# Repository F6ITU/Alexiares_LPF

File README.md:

# Alexiares_LPF
This repository contains the up to date version of the OpenHPSDR Low Pass Filter project(Alexiares frontend). 

**Important notice** : please check the "Branch" pull-down menu to see the different versions of the pcb

This work is protected by the TAPR Open Hardware Licence https://www.tapr.org/ohl.html

Original work by Graham Haddock, KE9H and Phil Harman, VK6APH.

3D image of the board are stored in the "images" folder (3D and pcb planes)

This folder also include "real life" pictures of the board, Vector Analyzer capture of the filter's characteristics and a pdf file of the schematic

Board's dimensions 10x15cm , 4 layers

So far, the Alex project under Kicad contains: 

AlexI2C

Alexandrie 

Alexiares_Coax_Out

Alexiares_HPF

Alexiares_LPF (this one)

Mentor

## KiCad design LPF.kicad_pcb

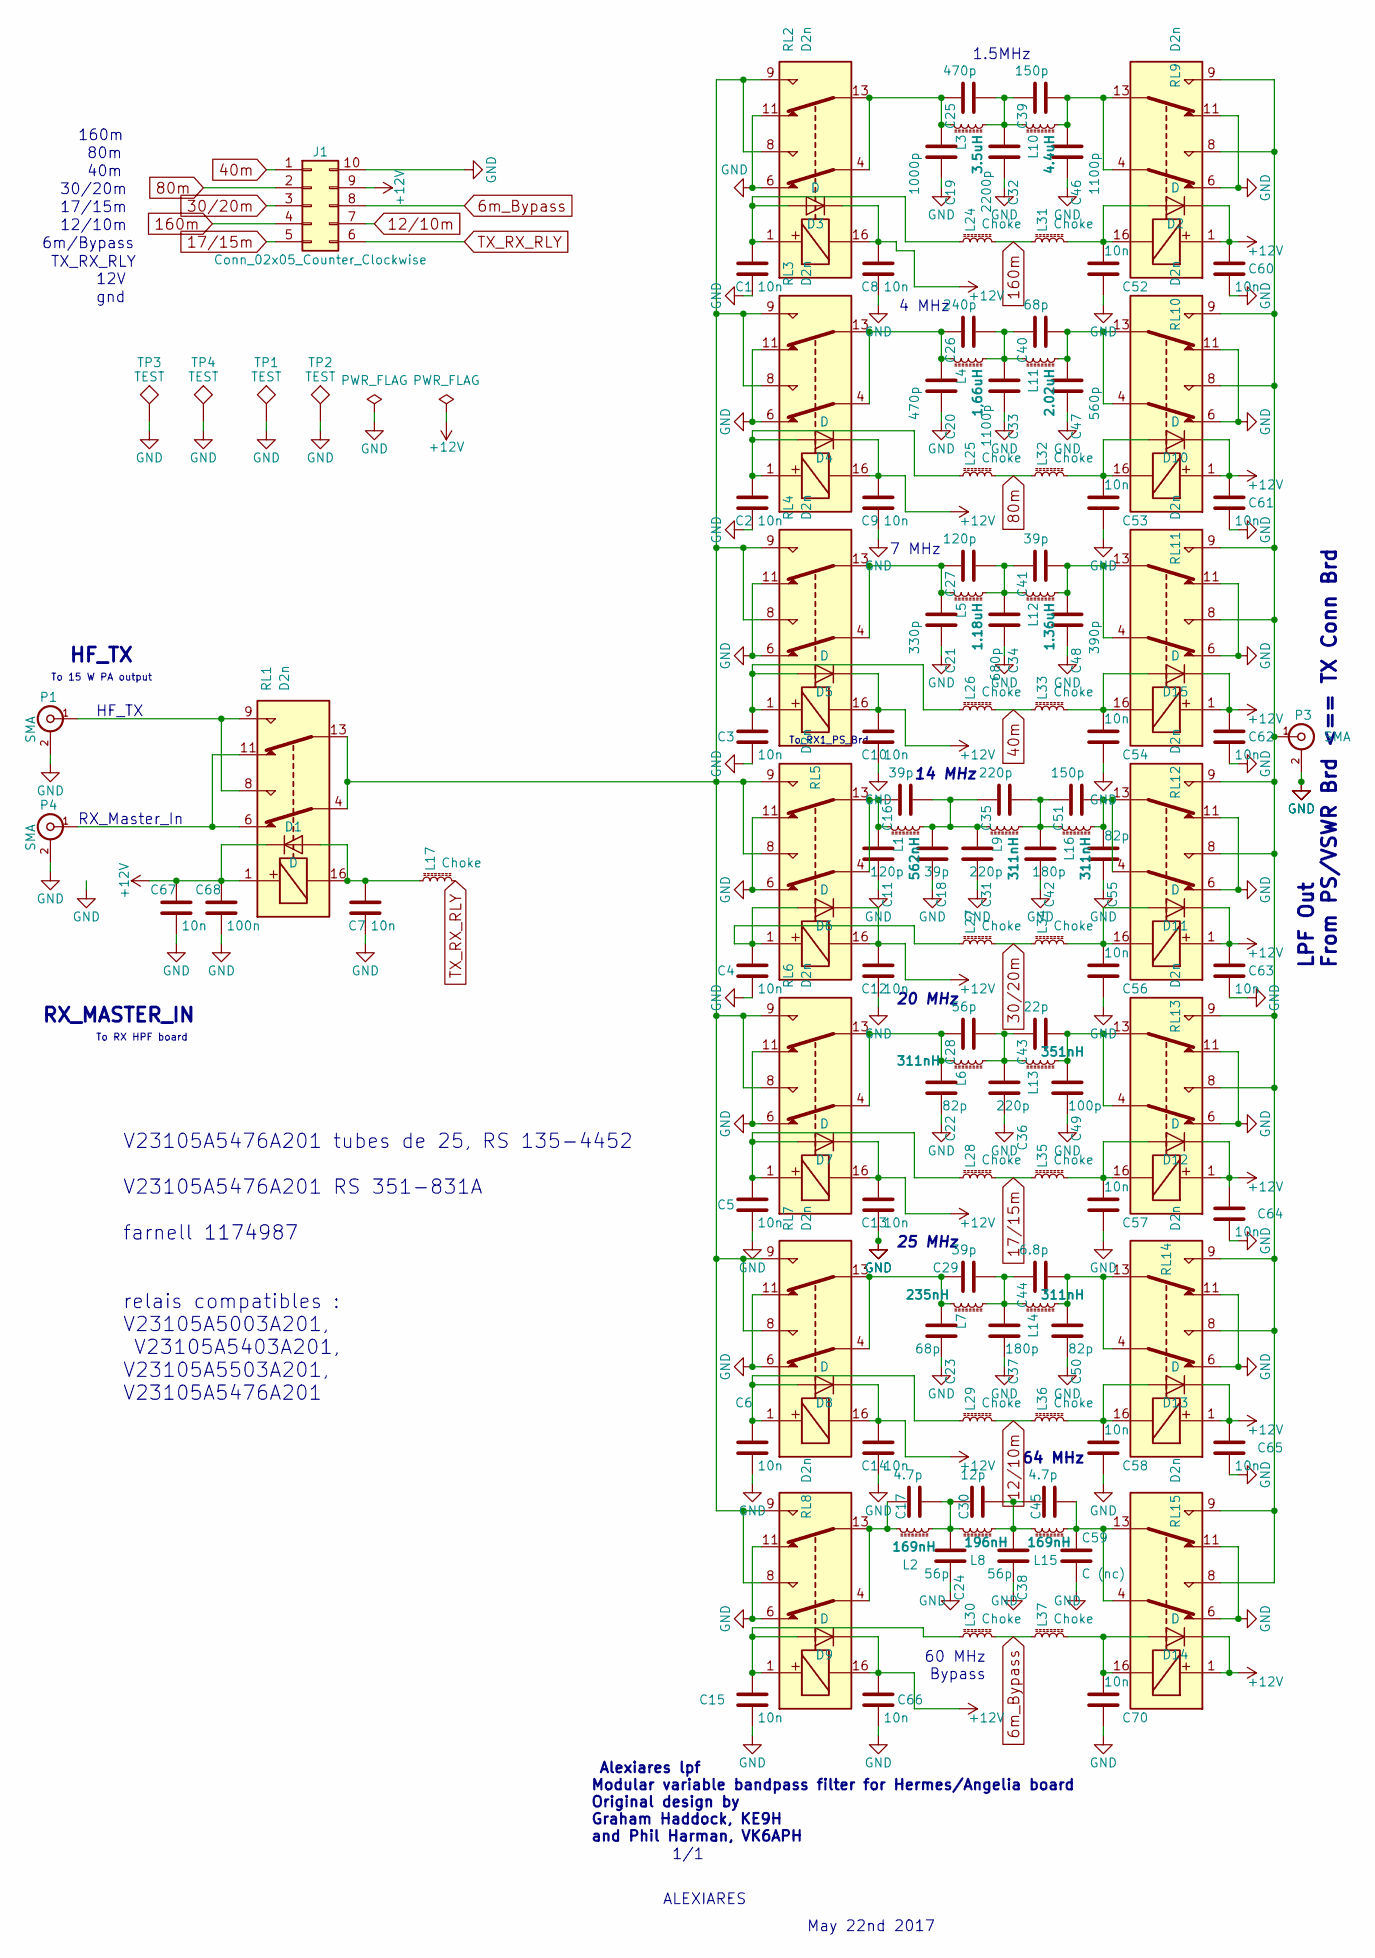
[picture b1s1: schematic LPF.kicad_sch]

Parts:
C1, C2, C3, C4, C5, C6, C7, C8, C9, C10, C12, C13, C14, C15, C52, C53, C54, C56, C57, C58, C60, C61, C62, C63, C64, C65, C66, C67, C70: 10n; C_0805_2012Metric_Pad1.15x1.40mm_HandSolder
C11, C27: 120p; ATC_500_HandSoldering
C16, C18, C29, C41: 39p; ATC_500_HandSoldering
C17, C45: 4.7p; ATC_500_HandSoldering
C19: 1000p; ATC_500_HandSoldering
C20, C25: 470p; ATC_500_HandSoldering
C21: 330p; ATC_500_HandSoldering
C22, C50, C55: 82p; ATC_500_HandSoldering
C23, C40: 68p; ATC_500_HandSoldering
C24, C28, C38: 56p; ATC_500_HandSoldering
C26: 240p; ATC_500_HandSoldering
C30: 12p; ATC_500_HandSoldering
C31, C35, C36: 220p; ATC_500_HandSoldering
C32: 2200p; ATC_500_HandSoldering
C33, C46: 1100p; ATC_500_HandSoldering
C34: 680p; ATC_500_HandSoldering
C37, C42: 180p; ATC_500_HandSoldering
C39, C51: 150p; ATC_500_HandSoldering
C43: 22p; ATC_500_HandSoldering
C44: 6.8p; ATC_500_HandSoldering
C47: 560p; ATC_500_HandSoldering
C48: 390p; ATC_500_HandSoldering
C49: 100p; ATC_500_HandSoldering
C59: C (nc); ATC_500_HandSoldering
C68: 100n; C_0805_2012Metric_Pad1.15x1.40mm_HandSolder
D1, D2, D3, D4, D5, D6, D7, D8, D9, D10, D11, D12, D13, D14, D15: D; D_SMB
J1: Conn_02x05_Counter_Clockwise; PinHeader_2x05_P2.54mm_Vertical
L1: 562nH; T50_V_THT
L2, L15: 169nH; T50_V_THT
L3: 3.5uH; T50_V_THT
L4: 1,66uH; T50_V_THT
L5: 1.18uH; T50_V_THT
L6, L9, L14, L16: 311nH; T50_V_THT
L7: 235nH; T50_V_THT
L8: 196nH; T50_V_THT
L10: 4.4uH; T50_V_THT
L11: 2.02uH; T50_V_THT
L12: 1.36uH; T50_V_THT
L13: 351nH; T50_V_THT
L17, L24, L25, L26, L27, L28, L29, L30, L31, L32, L33, L34, L35, L36, L37: Choke; L_0805_2012Metric_Pad1.15x1.40mm_HandSolder
P1, P3, P4: SMA; SMA_PINS
RL1, RL2, RL3, RL4, RL5, RL6, RL7, RL8, RL9, RL10, RL11, RL12, RL13, RL14, RL15: D2n
TP1, TP2, TP3, TP4: TEST; MountingHole_3.5mm_Pad

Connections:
6m_Bypass: J1.8, L30.2, L37.1
12/10m: J1.7, L29.2, L36.1
17/15m: J1.5, L28.2, L35.1
30/20m: J1.3, L27.2, L34.1
40m: J1.1, L26.2, L33.1
80m: J1.2, L25.2, L32.1
160m: J1.4, L24.2, L31.1
+12V: C8.1, C9.1, C10.1, C12.1, C13.1, C14.1, C60.1, C61.1, C62.1, C63.1, C64.1, C65.1, C66.1, C67.1, C68.1, D1.1 (K), D2.1 (K), D3.1 (K), D4.1 (K), D5.1 (K), D6.1 (K), D7.1 (K), D8.1 (K), D9.1 (K), D10.1 (K), D11.1 (K), D12.1 (K), D13.1 (K), D14.1 (K), D15.1 (K), J1.9, RL1.1, RL2.16, RL3.16, RL4.16, RL5.16, RL6.16, RL7.16, RL8.16, RL9.1, RL10.1, RL11.1, RL12.1, RL13.1, RL14.1, RL15.1
GND: C1.2, C2.2, C3.2, C4.2, C5.2, C6.2, C7.2, C8.2, C9.2, C10.2, C11.1, C12.2, C13.2, C14.2, C15.2, C18.1, C19.1, C20.1, C21.1, C22.1, C23.1, C24.1, C31.1, C32.1, C33.1, C34.1, C36.1, C37.1, C38.1, C42.1, C46.1, C47.1, C48.1, C49.1, C50.1, C52.1, C53.1, C54.1, C55.1, C56.1, C57.1, C58.1, C59.2, C60.2, C61.2, C62.2, C63.2, C64.2, C65.2, C66.2, C67.2, C68.2, C70.1, J1.10, P1.2 (Ext), P3.2 (Ext), P4.2 (Ext), RL2.6, RL2.11, RL3.6, RL3.11, RL4.6, RL4.11, RL5.6, RL5.11, RL6.6, RL6.11, RL7.6, RL7.11, RL8.6, RL8.11, RL9.6, RL9.11, RL10.6, RL10.11, RL11.6, RL11.11, RL12.6, RL12.11, RL13.6, RL13.11, RL14.6, RL14.11, RL15.6, RL15.11, TP1.1, TP2.1, TP3.1, TP4.1
unnamed: C1.1, D3.2 (A), L24.1, RL2.1
unnamed: C2.1, D4.2 (A), L25.1, RL3.1
unnamed: C3.1, D5.2 (A), L26.1, RL4.1
unnamed: C4.1, D6.2 (A), L27.1, RL5.1
unnamed: C5.1, D7.2 (A), L28.1, RL6.1
unnamed: C6.1, D8.2 (A), L29.1, RL7.1
unnamed: C7.1, D1.2 (A), L17.1, RL1.16
unnamed: C11.2, C16.1, L1.1, RL5.4, RL5.13
unnamed: C15.1, D9.2 (A), L30.1, RL8.1
unnamed: C16.2, C18.2, C31.2, C35.1, L1.2, L9.1
unnamed: C17.1, L2.1, RL8.4, RL8.13
unnamed: C17.2, C24.2, C30.1, L2.2, L8.1
unnamed: C19.2, C25.1, L3.1, RL2.4, RL2.13
unnamed: C20.2, C26.1, L4.1, RL3.4, RL3.13
unnamed: C21.2, C27.1, L5.1, RL4.4, RL4.13
unnamed: C22.2, C28.1, L6.1, RL6.4, RL6.13
unnamed: C23.2, C29.1, L7.1, RL7.4, RL7.13
unnamed: C25.2, C32.2, C39.1, L3.2, L10.1
unnamed: C26.2, C33.2, C40.1, L4.2, L11.1
unnamed: C27.2, C34.2, C41.1, L5.2, L12.1
unnamed: C28.2, C36.2, C43.1, L6.2, L13.1
unnamed: C29.2, C37.2, C44.1, L7.2, L14.1
unnamed: C30.2, C38.2, C45.1, L8.2, L15.1
unnamed: C35.2, C42.2, C51.1, L9.2, L16.1
unnamed: C39.2, C46.2, L10.2, RL9.4, RL9.13
unnamed: C40.2, C47.2, L11.2, RL10.4, RL10.13
unnamed: C41.2, C48.2, L12.2, RL11.4, RL11.13
unnamed: C43.2, C49.2, L13.2, RL13.4, RL13.13
unnamed: C44.2, C50.2, L14.2, RL14.4, RL14.13
unnamed: C45.2, C59.1, L15.2, RL15.4, RL15.13
unnamed: C51.2, C55.2, L16.2, RL12.4, RL12.13
unnamed: C52.2, D2.2 (A), L31.2, RL9.16
unnamed: C53.2, D10.2 (A), L32.2, RL10.16
unnamed: C54.2, D15.2 (A), L33.2, RL11.16
unnamed: C56.2, D11.2 (A), L34.2, RL12.16
unnamed: C57.2, D12.2 (A), L35.2, RL13.16
unnamed: C58.2, D13.2 (A), L36.2, RL14.16
unnamed: C70.2, D14.2 (A), L37.2, RL15.16
unnamed: P1.1 (In), RL1.8, RL1.9
unnamed: P3.1 (In), RL9.8, RL9.9, RL10.8, RL10.9, RL11.8, RL11.9, RL12.8, RL12.9, RL13.8, RL13.9, RL14.8, RL14.9, RL15.8, RL15.9
unnamed: P4.1 (In), RL1.6, RL1.11
unnamed: RL1.4, RL1.13, RL2.8, RL2.9, RL3.8, RL3.9, RL4.8, RL4.9, RL5.8, RL5.9, RL6.8, RL6.9, RL7.8, RL7.9, RL8.8, RL8.9
TX_RX_RLY: J1.6, L17.2

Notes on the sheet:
gnd
25 MHz
30/20m
TX_RX_RLY
12V
ALEXIARES
160m
6m/Bypass
1/1
14 MHz
4 MHz
80m
V23105A5476A201 tubes de 25, RS 135-4452 V23105A5476A201 RS 351-831A farnell 1174987 relais compatibles : V23105A5003A201, V23105A5403A201, V23105A5503A201, V23105A5476A201
To_RX1_PS_Brd
17/15m
To 15 W PA output
1.5MHz
RX_Master_In
RX_MASTER_IN
64 MHz
LPF Out From PS/VSWR Brd <== TX Conn Brd
Alexiares lpf Modular variable bandpass filter for Hermes/Angelia board Original design by Graham Haddock, KE9H and Phil Harman, VK6APH
May 22nd 2017
HF_TX
7 MHz
20 MHz
40m
60 MHz Bypass
12/10m
To RX HPF board

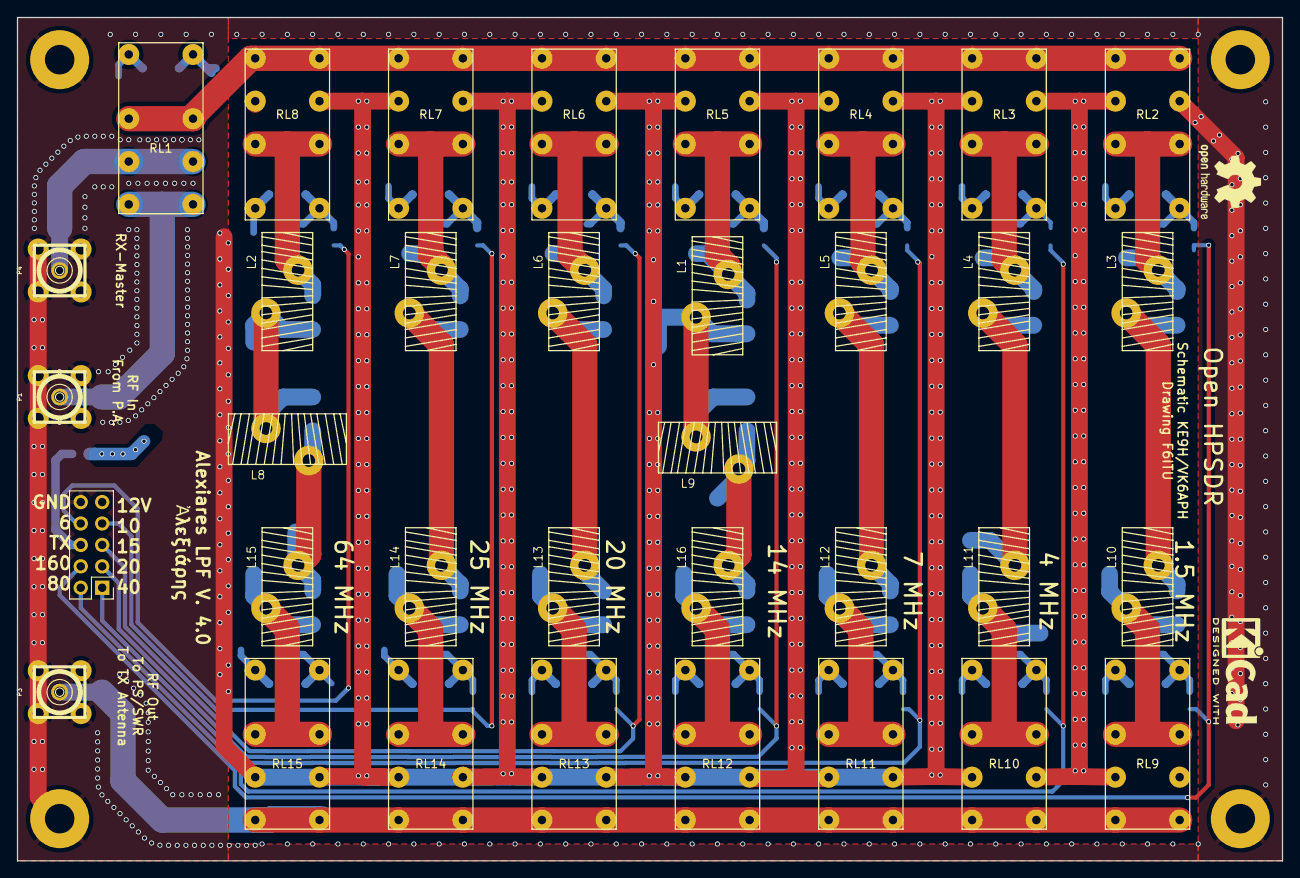
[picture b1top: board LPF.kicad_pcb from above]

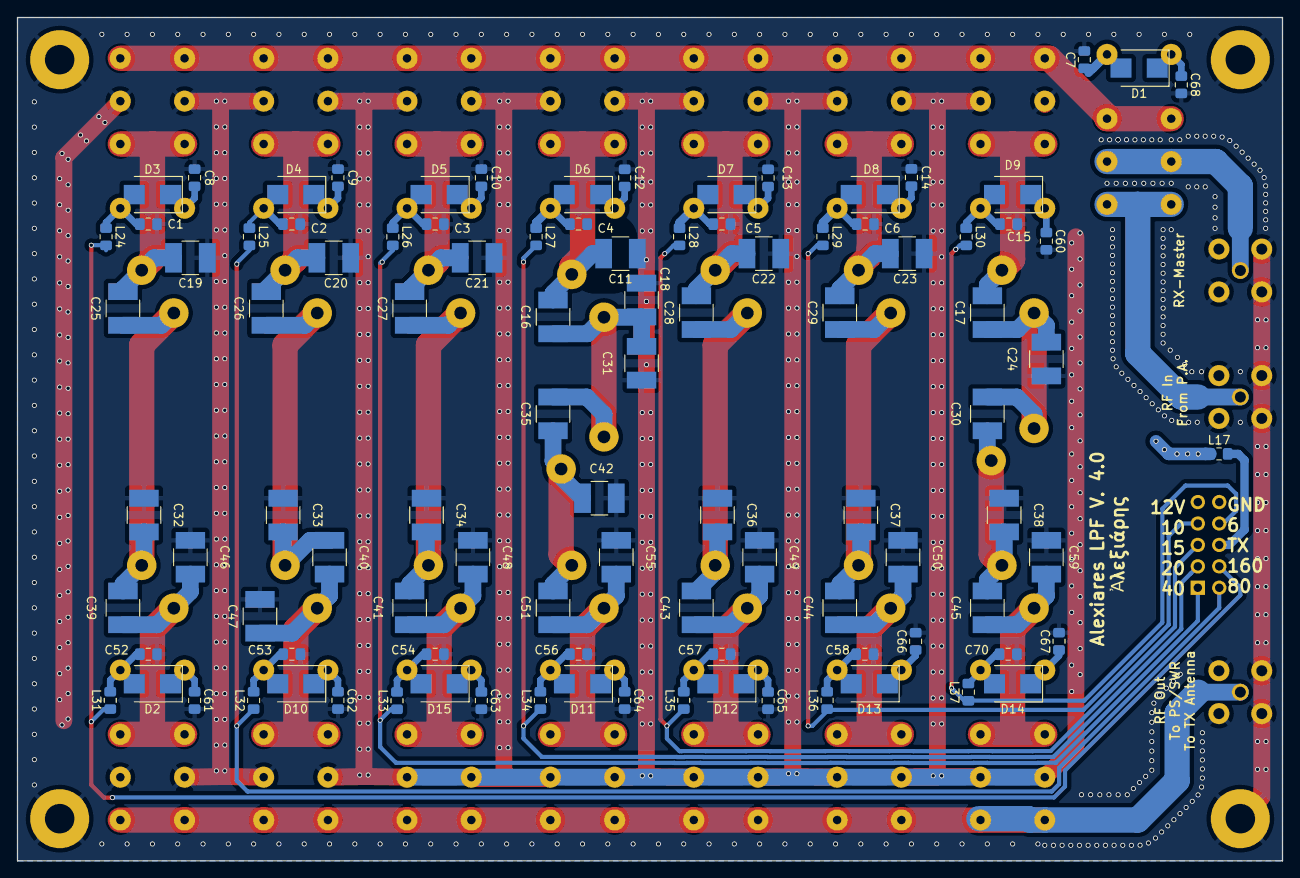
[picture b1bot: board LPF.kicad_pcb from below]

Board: 4 copper layers, 150.0 x 100.0 mm, 138 parts (99 on the bottom side), 52 nets.

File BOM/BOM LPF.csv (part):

Source:,C:\Users\marco\Documents\KiCad\Projets\Alexiares_LPF\LPF.sch,,,,,,
Date:,22/07/2020 10:55,,,,,,
Tool:,Eeschema (5.1.5)-3,,,,,,
Component Count:,134,,,,,,
Ref,Value,Footprint,Manufacturer,Type,Vendor,Reference,
C1,10n,Capacitor_SMD:C_0805_2012Metric_Pad1.15x1.40mm_HandSolder,Wurth Elektronik,MLCC,Mouser,710-885012207092,
C2,10n,Capacitor_SMD:C_0805_2012Metric_Pad1.15x1.40mm_HandSolder,Wurth Elektronik,MLCC,Mouser,710-885012207092,
C3,10n,Capacitor_SMD:C_0805_2012Metric_Pad1.15x1.40mm_HandSolder,Wurth Elektronik,MLCC,Mouser,710-885012207092,
C4,10n,Capacitor_SMD:C_0805_2012Metric_Pad1.15x1.40mm_HandSolder,Wurth Elektronik,MLCC,Mouser,710-885012207092,
C5,10n,Capacitor_SMD:C_0805_2012Metric_Pad1.15x1.40mm_HandSolder,Wurth Elektronik,MLCC,Mouser,710-885012207092,
C6,10n,Capacitor_SMD:C_0805_2012Metric_Pad1.15x1.40mm_HandSolder,Wurth Elektronik,MLCC,Mouser,710-885012207092,
C7,10n,Capacitor_SMD:C_0805_2012Metric_Pad1.15x1.40mm_HandSolder,Wurth Elektronik,MLCC,Mouser,710-885012207092,
C8,10n,Capacitor_SMD:C_0805_2012Metric_Pad1.15x1.40mm_HandSolder,Wurth Elektronik,MLCC,Mouser,710-885012207092,
C9,10n,Capacitor_SMD:C_0805_2012Metric_Pad1.15x1.40mm_HandSolder,Wurth Elektronik,MLCC,Mouser,710-885012207092,
C10,10n,Capacitor_SMD:C_0805_2012Metric_Pad1.15x1.40mm_HandSolder,Wurth Elektronik,MLCC,Mouser,710-885012207092,
C11,120p,Vishay HiFreq 1111 MLCC,Vishay Vitramon,MLCC 500V,Mouser,VJ1111D121KXGAT,
C12,10n,Capacitor_SMD:C_0805_2012Metric_Pad1.15x1.40mm_HandSolder,Wurth Elektronik,MLCC,Mouser,710-885012207092,
C13,10n,Capacitor_SMD:C_0805_2012Metric_Pad1.15x1.40mm_HandSolder,Wurth Elektronik,MLCC,Mouser,710-885012207092,
C14,10n,Capacitor_SMD:C_0805_2012Metric_Pad1.15x1.40mm_HandSolder,Wurth Elektronik,MLCC,Mouser,710-885012207092,
C15,10n,Capacitor_SMD:C_0805_2012Metric_Pad1.15x1.40mm_HandSolder,Wurth Elektronik,MLCC,Mouser,710-885012207092,
C16,39p,Vishay HiFreq 1111 MLCC,Vishay Vitramon,MLCC 500V,Mouser,VJ1111D390JXLAJ,
C17,4.7p,Vishay HiFreq 1111 MLCC,Vishay Vitramon,MLCC 500V,Mouser,VJ1111D4R7BXLQJ,
C18,39p,Vishay HiFreq 1111 MLCC,Vishay Vitramon,MLCC 500V,Mouser,VJ1111D390JXLAJ,
C19,1000p,Johanson,johanson 1812,MLCC 500V,Mouser,501S43N102JV4E,
C20,470p,Vishay HiFreq 1111 MLCC,Vishay Vitramon,MLCC 500V,Mouser,VJ1111D471KXLAJ,
C21,330p,Vishay HiFreq 1111 MLCC,Vishay Vitramon,MLCC 500V,Mouser,VJ1111D331JXLAJ,
C22,82p,Vishay HiFreq 1111 MLCC,Vishay Vitramon,MLCC 500V,Mouser,VJ1111D820GXGQJ,
C23,68p,Vishay HiFreq 1111 MLCC,Vishay Vitramon,MLCC 500V,Mouser,VJ1111D680GXLQJ,
C24,56p,Vishay HiFreq 1111 MLCC,Vishay Vitramon,MLCC 500V,Mouser,VJ1111D560GXLQJ,
C25,470p,Vishay HiFreq 1111 MLCC,Vishay Vitramon,MLCC 500V,Mouser,VJ1111D471KXLAJ,
C26,240p,Vishay HiFreq 1111 MLCC,Vishay Vitramon,MLCC 500V,Mouser,VJ1111D241JXLAJ,
C27,120p,Vishay HiFreq 1111 MLCC,Vishay Vitramon,MLCC 500V,Mouser,VJ1111D121KXGAT,
C28,56p,Vishay HiFreq 1111 MLCC,Vishay Vitramon,MLCC 500V,Mouser,VJ1111D560GXLQJ,
C29,39p,Vishay HiFreq 1111 MLCC,Vishay Vitramon,MLCC 500V,Mouser,VJ1111D390JXLAJ,
C30,12p,Vishay HiFreq 1111 MLCC,Vishay Vitramon,MLCC 500V,Mouser,VJ1111D120GLGQJ,
C31,220p,Vishay HiFreq 1111 MLCC,Vishay Vitramon,MLCC 500V,Mouser,VJ1111D221JXLAJ,
C32,2200p,Johanson,Johanson 1812,MLCC 1000V,Mouser,102S43N222KV4E,
C33,1100p,Vishay HiFreq 1111 MLCC,Vishay Vitramon,MLCC 500V,Mouser,VJ1111D102KXDAT,VJ1111D101JXLAJ
C34,680p,Johanson,johanson 1210,MLCC 1000V,Mouser,102S41N681KV4E,
C35,220p,Vishay HiFreq 1111 MLCC,Vishay Vitramon,MLCC 500V,Mouser,VJ1111D221JXLAJ,
C36,220p,Vishay HiFreq 1111 MLCC,Vishay Vitramon,MLCC 500V,Mouser,VJ1111D221JXLAJ,
C37,180p,Vishay HiFreq 1111 MLCC,Vishay Vitramon,MLCC 500V,Mouser,VJ1111D181JXLAJ,
C38,56p,Vishay HiFreq 1111 MLCC,Vishay Vitramon,MLCC 500V,Mouser,VJ1111D560GXLQJ,
C39,150p,Vishay HiFreq 1111 MLCC,Vishay Vitramon,MLCC 500V,Mouser,VJ1111D151GXLQJ,
C40,68p,Vishay HiFreq 1111 MLCC,Vishay Vitramon,MLCC 500V,Mouser,VJ1111D680GXLQJ,
C41,39p,Vishay HiFreq 1111 MLCC,Vishay Vitramon,MLCC 500V,Mouser,VJ1111D390JXLAJ,
C42,180p,Vishay HiFreq 1111 MLCC,Vishay Vitramon,MLCC 500V,Mouser,VJ1111D181JXLAJ,
C43,22p,Vishay HiFreq 1111 MLCC,Vishay Vitramon,MLCC 500V,Mouser,VJ1111D220GLLQJ,
C44,6.8p,Vishay HiFreq 1111 MLCC,Vishay Vitramon,MLCC 500V,Mouser,VJ1111D6R8BXGQJ,
C45,4.7p,Vishay HiFreq 1111 MLCC,Vishay Vitramon,MLCC 500V,Mouser,VJ1111D4R7BXLQ,
C46,1100p,Vishay HiFreq 1111 MLCC,Vishay Vitramon,MLCC 500V,Mouser,VJ1111D102KXDAT,VJ1111D101JXLAJ
C47,560p,Johanson,Johanson 1210,MLCC 500V,Mouser,501S41N561KV4E,
C48,390p,Vishay HiFreq 1111 MLCC,Vishay Vitramon,MLCC 500V,Mouser,VJ1111D391KXLAJ,
C49,100p,Vishay HiFreq 1111 MLCC,Vishay Vitramon,MLCC 500V,Mouser,VJ1111D101JXLAJ,
C50,82p,Vishay HiFreq 1111 MLCC,Vishay Vitramon,MLCC 500V,Mouser,VJ1111D820GXGQJ,
C51,150p,Vishay HiFreq 1111 MLCC,Vishay Vitramon,MLCC 500V,Mouser,VJ1111D151GXLQJ,
C52,10n,Capacitor_SMD:C_0805_2012Metric_Pad1.15x1.40mm_HandSolder,Wurth Elektronik,MLCC,Mouser,710-885012207092,
C53,10n,Capacitor_SMD:C_0805_2012Metric_Pad1.15x1.40mm_HandSolder,Wurth Elektronik,MLCC,Mouser,710-885012207092,
C54,10n,Capacitor_SMD:C_0805_2012Metric_Pad1.15x1.40mm_HandSolder,Wurth Elektronik,MLCC,Mouser,710-885012207092,
C55,82p,Capacitor_SMD:C_0805_2012Metric_Pad1.15x1.40mm_HandSolder,Wurth Elektronik,MLCC,Mouser,VJ1111D820GXGQJ,
C56,10n,Capacitor_SMD:C_0805_2012Metric_Pad1.15x1.40mm_HandSolder,Wurth Elektronik,MLCC,Mouser,710-885012207092,
C57,10n,Capacitor_SMD:C_0805_2012Metric_Pad1.15x1.40mm_HandSolder,Wurth Elektronik,MLCC,Mouser,710-885012207092,
C58,10n,Capacitor_SMD:C_0805_2012Metric_Pad1.15x1.40mm_HandSolder,Wurth Elektronik,MLCC,Mouser,710-885012207092,
C59,C (nc),ATC_B:ATC_500_HandSoldering,,,,,
C60,10n,Capacitor_SMD:C_0805_2012Metric_Pad1.15x1.40mm_HandSolder,Wurth Elektronik,MLCC,Mouser,710-885012207092,
C61,10n,Capacitor_SMD:C_0805_2012Metric_Pad1.15x1.40mm_HandSolder,Wurth Elektronik,MLCC,Mouser,710-885012207092,
C62,10n,Capacitor_SMD:C_0805_2012Metric_Pad1.15x1.40mm_HandSolder,Wurth Elektronik,MLCC,Mouser,710-885012207092,
C63,10n,Capacitor_SMD:C_0805_2012Metric_Pad1.15x1.40mm_HandSolder,Wurth Elektronik,MLCC,Mouser,710-885012207092,
C64,10n,Capacitor_SMD:C_0805_2012Metric_Pad1.15x1.40mm_HandSolder,Wurth Elektronik,MLCC,Mouser,710-885012207092,
C65,10n,Capacitor_SMD:C_0805_2012Metric_Pad1.15x1.40mm_HandSolder,Wurth Elektronik,MLCC,Mouser,710-885012207092,
C66,10n,Capacitor_SMD:C_0805_2012Metric_Pad1.15x1.40mm_HandSolder,Wurth Elektronik,MLCC,Mouser,710-885012207092,
C67,10n,Capacitor_SMD:C_0805_2012Metric_Pad1.15x1.40mm_HandSolder,Wurth Elektronik,MLCC,Mouser,710-885012207092,
C68,100n,Capacitor_SMD:C_0805_2012Metric_Pad1.15x1.40mm_HandSolder,Wurth Elektronik,MLCC,Mouser,710-885012207092,
C70,10n,Capacitor_SMD:C_0805_2012Metric_Pad1.15x1.40mm_HandSolder,Wurth Elektronik,MLCC,Mouser,710-885012207092,
D1,D,Diode_SMD:D_SMB,Comchip,Schottky SS24 (DO214),Mouser,750-SS24B-HF,
D2,D,Diode_SMD:D_SMB,Comchip,Schottky SS24 (DO214),Mouser,750-SS24B-HF,
D3,D,Diode_SMD:D_SMB,Comchip,Schottky SS24 (DO214),Mouser,750-SS24B-HF,
D4,D,Diode_SMD:D_SMB,Comchip,Schottky SS24 (DO214),Mouser,750-SS24B-HF,
D5,D,Diode_SMD:D_SMB,Comchip,Schottky SS24 (DO214),Mouser,750-SS24B-HF,
D6,D,Diode_SMD:D_SMB,Comchip,Schottky SS24 (DO214),Mouser,750-SS24B-HF,
D7,D,Diode_SMD:D_SMB,Comchip,Schottky SS24 (DO214),Mouser,750-SS24B-HF,
D8,D,Diode_SMD:D_SMB,Comchip,Schottky SS24 (DO214),Mouser,750-SS24B-HF,
D9,D,Diode_SMD:D_SMB,Comchip,Schottky SS24 (DO214),Mouser,750-SS24B-HF,
D10,D,Diode_SMD:D_SMB,Comchip,Schottky SS24 (DO214),Mouser,750-SS24B-HF,
D11,D,Diode_SMD:D_SMB,Comchip,Schottky SS24 (DO214),Mouser,750-SS24B-HF,
D12,D,Diode_SMD:D_SMB,Comchip,Schottky SS24 (DO214),Mouser,750-SS24B-HF,
D13,D,Diode_SMD:D_SMB,Comchip,Schottky SS24 (DO214),Mouser,750-SS24B-HF,
D14,D,Diode_SMD:D_SMB,Comchip,Schottky SS24 (DO214),Mouser,750-SS24B-HF,
D15,D,Diode_SMD:D_SMB,Comchip,Schottky SS24 (DO214),Mouser,750-SS24B-HF,
J1,Conn_02x05_Counter_Clockwise,Connector_PinHeader_2.54mm:PinHeader_2x05_P2.54mm_Vertical,,,,,
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
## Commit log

2017-06-12 lpf V1.0, compatible w OpenHPSDR Ver24
2017-09-14 version 1.1
2017-11-01 minor changes, adding kk lib, still under dev.
2017-11-04 new 4 layers routing, mods in schematic
2017-11-05 decoupling & freewheeling routing
2017-11-06 RTM 2, silk corrected, via added, jpg image and readme added
2017-11-10 added choke ferrite on each command line
2017-11-14 Caps changed for ATC-B footprint. Under dev., unstable
2017-11-15 new routing after ATC100B change, RTM2
2017-11-27 minor routing changes, via added
2017-12-10 add forbiden zone under bypass power caps
2017-12-12 trace cleaning, SMA edge added, main connector rotated
2017-12-16 changed sma footprint, gerber done
2018-01-05 stitching and new gerber
2018-01-06 new stitching, new gerber
2018-01-08 stitching errors corrected, new gerber
2018-01-09 BOM added, new Gerber
2018-01-12 hunting some last bugs, new gerber
2018-01-21 new LNA design
2018-01-24 bom changed
2018-02-12 chasing routing errors
2018-02-12 hunting smal bugs
2018-02-12 hunting last soldermask errors
2018-05-08 inductance value modified
2018-06-27 minor silk changes
2018-06-27 lpf V1 stable release (pse use the V2 instead)
2018-06-29 cleaning for V 2.0 version
2018-07-05 minor change in 160m relay position, V2.0 ready
2019-03-15 upgrate to Kicad 5.0n, new up to date Gerber
2019-04-06 V 3.0, 54 MHz lpf now online
2020-05-03 version 3 provisoire
2020-05-03 version 3 provisoire git status
2020-05-03 version 4 en dimension 10x15
2020-05-03 day to day cleaning, anciliary tasks
2020-05-04 new readme
2020-07-21 file update and cleaning July 21
2020-07-21 some more cleaning
2020-07-21 gerber totally erased
2020-07-21 updated Gerber files & ibom
2020-07-21 cleaning deprecated files
2020-07-22 removing deprecated files
2020-07-22 search old and destroy
2020-07-22 lpf v4.0 file update
2020-07-22 minor cleaning of LPF v4.0 schematic files
2020-07-22 Excel and csv BOM files added
2020-07-22 bom cleaning
2020-07-22 new Excel BOM
2023-04-16 new routing enhancing eddy currents
2025-08-06 minor changes, 1 bug fixed
